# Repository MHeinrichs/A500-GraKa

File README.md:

[This project moved to gitlab on the day M$ bought github](https://gitlab.com/MHeinrichs/A500-GraKa)

The new repository is at: https://gitlab.com/MHeinrichs/A500-GraKa

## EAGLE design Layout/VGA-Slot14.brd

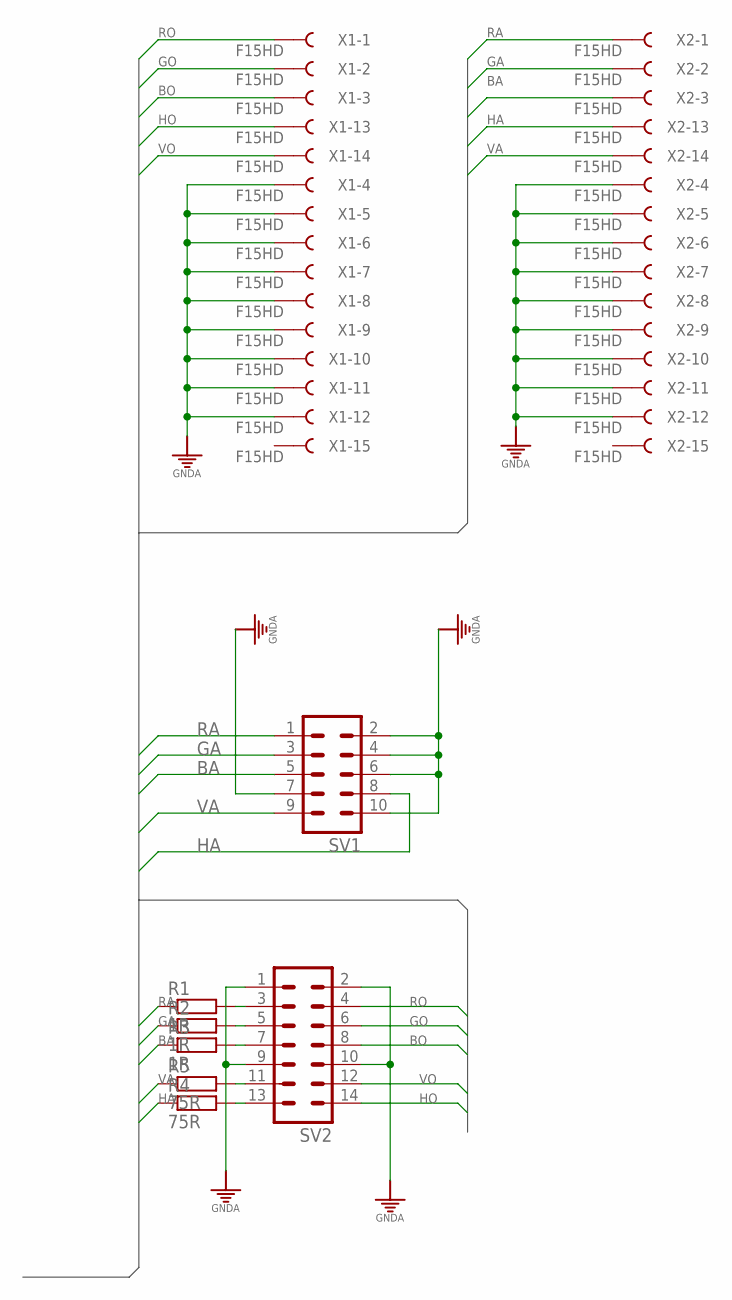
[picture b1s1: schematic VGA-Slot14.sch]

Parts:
R1, R2, R3: 1R; R0805
R4, R5: 75R; R0805
SV1: ML10
SV2: ML14
X1, X2: F15HD

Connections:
BA: R3.1, SV1.5, X2.3
BO: SV2.8, X1.3
GA: R2.1, SV1.3, X2.2
GNDA: SV1.2, SV1.4, SV1.6, SV1.7, SV1.10, SV2.1, SV2.2, SV2.9, SV2.10, X1.4, X1.5, X1.6, X1.7, X1.8, X1.9, X1.10, X1.11, X1.12, X2.4, X2.5, X2.6, X2.7, X2.8, X2.9, X2.10, X2.11, X2.12
GO: SV2.6, X1.2
HA: R4.1, SV1.8, X2.13
HO: SV2.14, X1.13
unnamed: R2.2, SV2.5
unnamed: R1.2, SV2.3
unnamed: R3.2, SV2.7
unnamed: R5.2, SV2.11
unnamed: R4.2, SV2.13
RA: R1.1, SV1.1, X2.1
RO: SV2.4, X1.1
VA: R5.1, SV1.9, X2.14
VO: SV2.12, X1.14

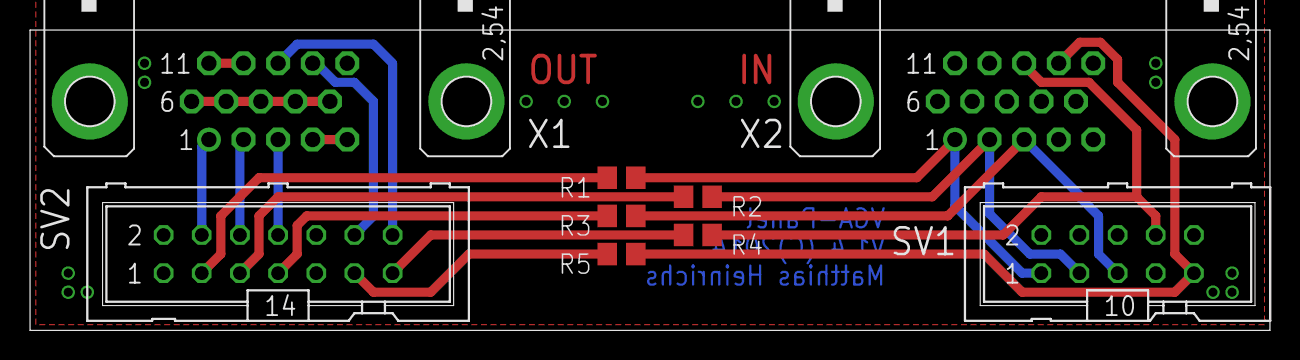
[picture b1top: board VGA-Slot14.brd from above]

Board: 2 copper layers, 82.5 x 20.0 mm, 9 parts (0 on the bottom side), 16 nets.

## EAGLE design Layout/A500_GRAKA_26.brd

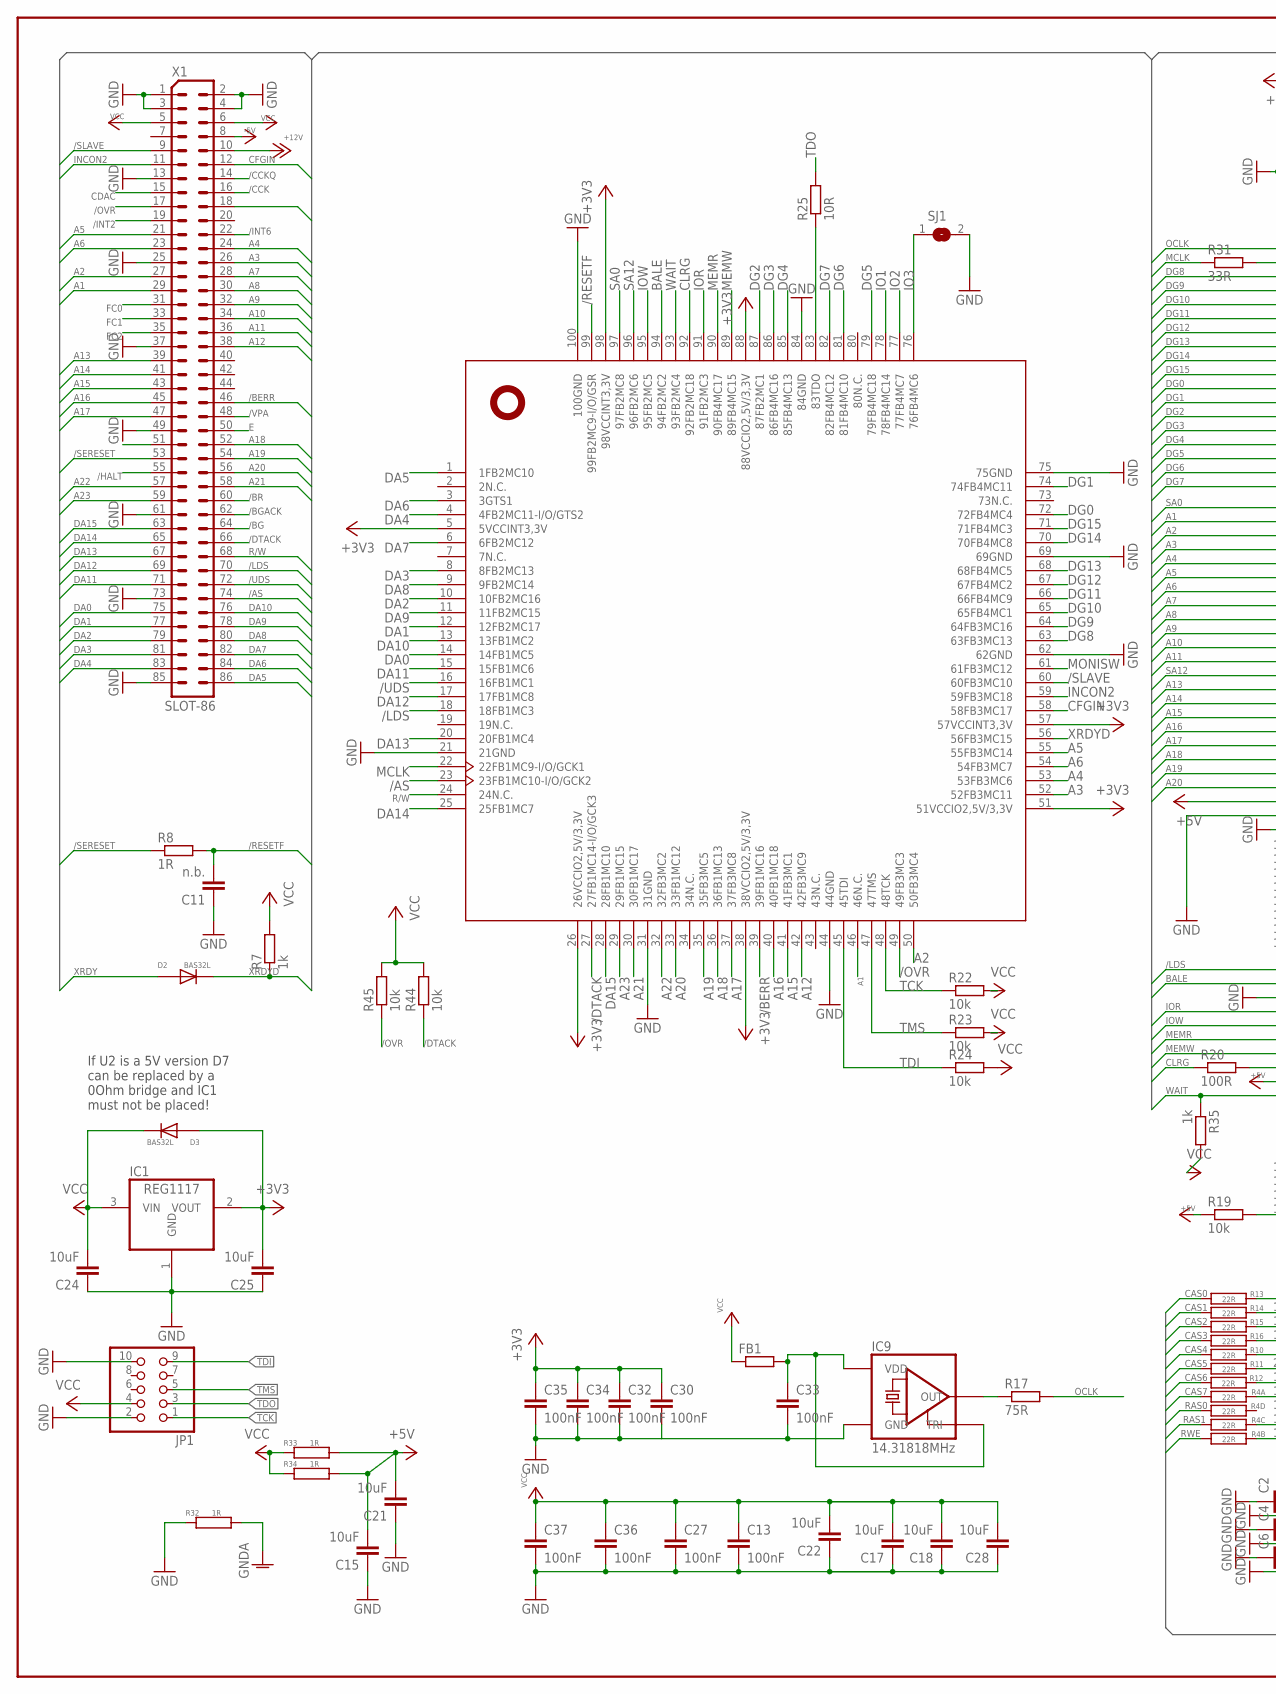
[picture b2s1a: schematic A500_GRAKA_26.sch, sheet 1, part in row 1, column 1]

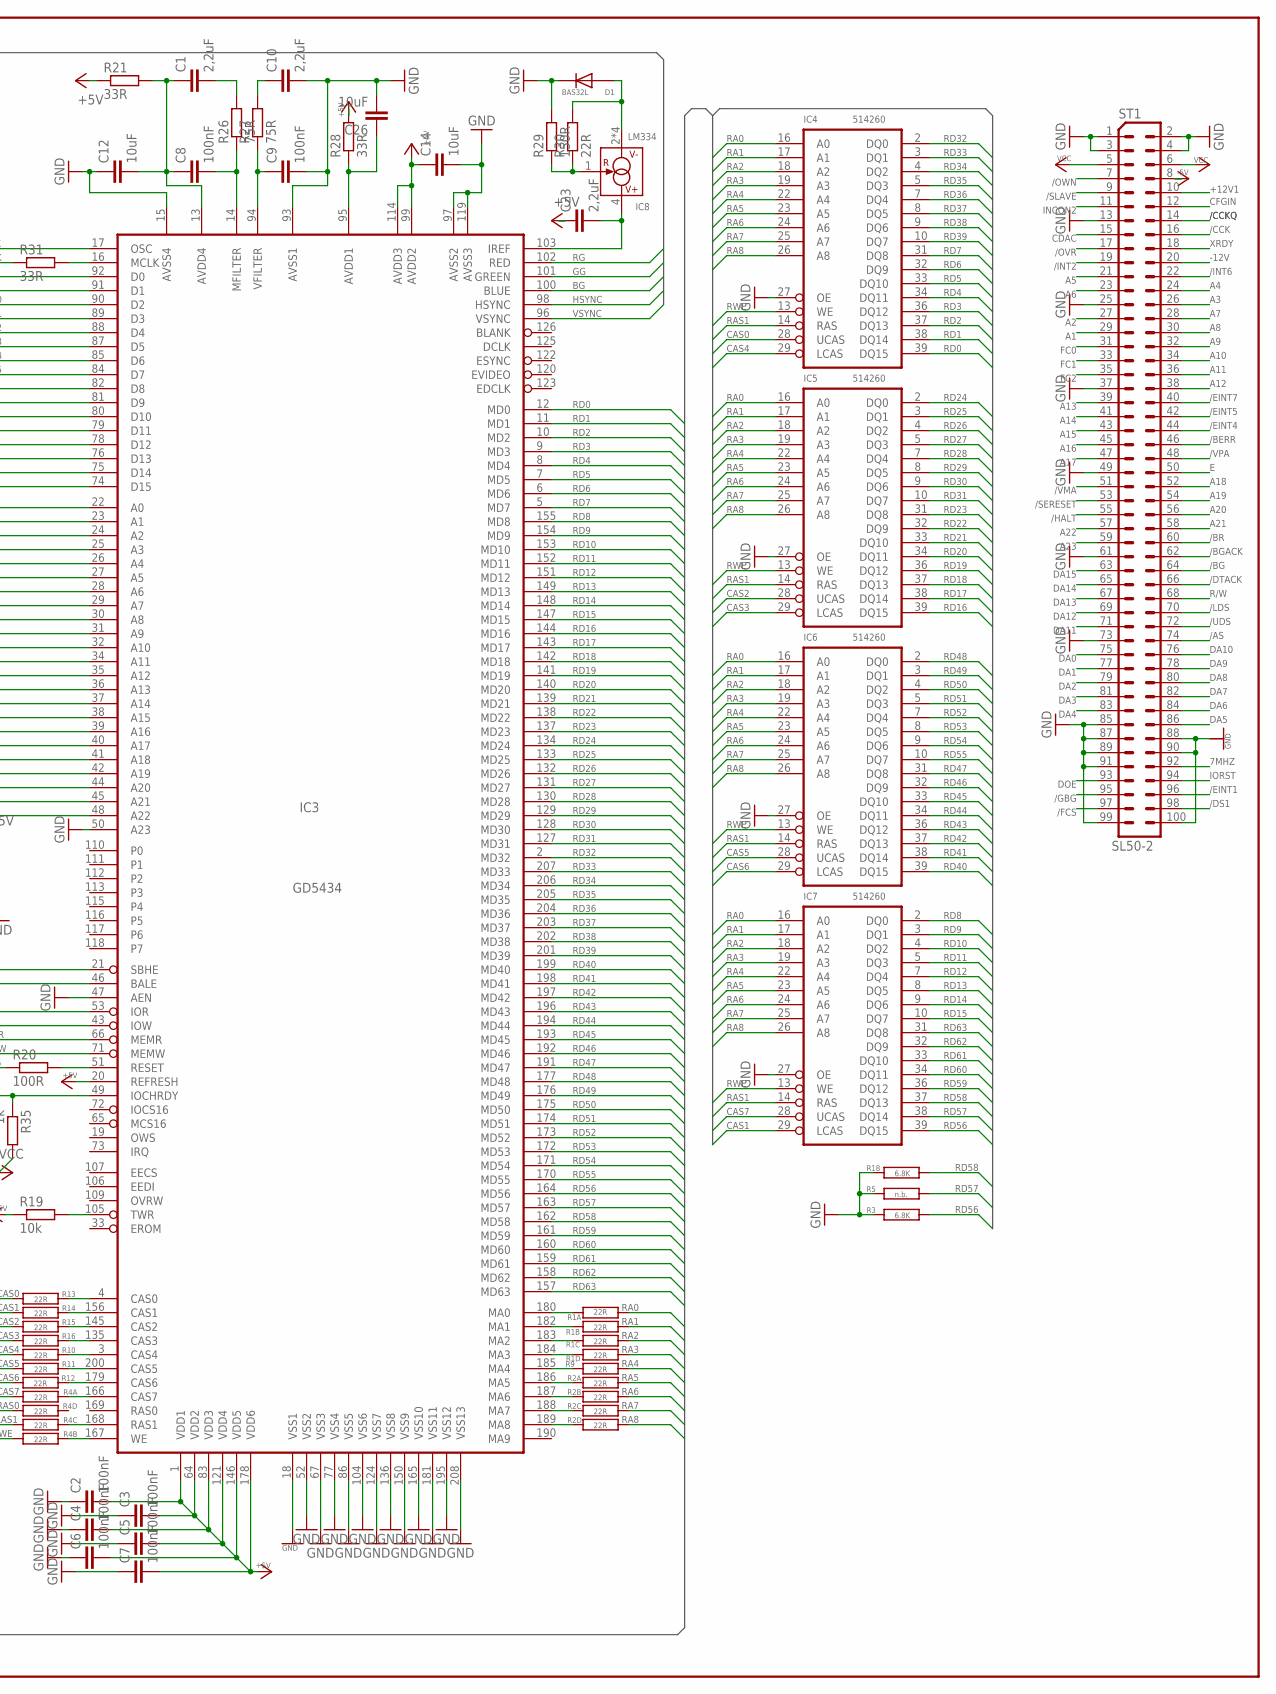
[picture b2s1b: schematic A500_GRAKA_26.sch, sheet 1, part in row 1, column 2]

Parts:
C1, C10, C23: 2,2uF; C0805K
C2, C3, C4, C5, C6, C7, C8, C9, C13, C27, C30, C32, C33, C34, C35, C36, C37: 100nF; C0805K
C11: n.b.; C0805K
C12, C14, C15, C17, C18, C21, C22, C24, C25, C26, C28: 10uF; C0805K
D1, D2, D3: BAS32L; SOD-80
FB1: R-EU_R0805; R0805
IC1: REG1117; SOT223
IC2: XC95144XLTQ100; TQ100
IC3: GD5434; PQFP-208@3
IC4, IC5, IC6, IC7: 514260; SOJ40/4
IC8: LM334; SO08
IC9: 14.31818MHz; 7X5
JP1: PINHD-2X5_2.54-SMD; 2X05SMD
R1, R2, R4: 22R; R-NETZ
R3, R18: 6.8K; 0805@2
R5: n.b.; 0805@2
R7, R35: 1k; R0805
R8: 1R; R0805
R9, R10, R11, R12, R13, R14, R15, R16: 22R; 0805@2
R17, R26, R27: 75R; R0805
R19, R22, R23, R24, R44, R45: 10k; R0805
R20: 100R; R0805
R21, R28, R31: 33R; R0805
R25: 10R; R0805
R29: 150R; R0805
R30: 22R; R0805
R32, R33, R34: 1R; 0204
SJ1: SJ
ST1: SL50-2; LKOT-501
X1: SLOT-86

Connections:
7MHZ: ST1.92
+3V3: C25.2, C30.1, C32.1, C34.1, C35.1, D3.1 (A), IC1.2 (VOUT), IC2.5 (5VCCINT3,3V), IC2.26 (26VCCIO2,5V/3,3V), IC2.38 (38VCCIO2,5V/3,3V), IC2.51 (51VCCIO2,5V/3,3V), IC2.57 (57VCCINT3,3V), IC2.88 (88VCCIO2,5V/3,3V), IC2.98 (98VCCINT3,3V)
+5V: C2.2, C3.2, C4.2, C5.2, C6.2, C7.2, C14.1, C15.2, C21.2, C23.1, IC3.1 (VDD1), IC3.20 (REFRESH), IC3.45 (A21), IC3.64 (VDD2), IC3.83 (VDD3), IC3.99 (AVDD2), IC3.114 (AVDD3), IC3.121 (VDD4), IC3.146 (VDD5), IC3.178 (VDD6), R19.1, R21.1, R28.2, R33.1, R34.1
+12V: X1.10
+12V1: ST1.10
-5V: ST1.8, X1.8
-12V: ST1.20
/AS: IC2.23 (23FB1MC10-I/O/GCK2), ST1.74, X1.74
/BERR: IC2.39 (39FB1MC16), ST1.46, X1.46
/BG: ST1.64, X1.64
/BGACK: ST1.62, X1.62
/BR: ST1.60, X1.60
/CCK: ST1.16, X1.16
/CCKQ: ST1.14, X1.14
/DS1: ST1.98
/DTACK: IC2.27 (27FB1MC14-I/O/GCK3), R44.1, ST1.66, X1.66
/EINT1: ST1.96
/EINT4: ST1.44
/EINT5: ST1.42
/EINT7: ST1.40
/FCS: ST1.97
/GBG: ST1.95
/HALT: ST1.55, X1.55
/INT2: ST1.19, X1.19
/INT6: ST1.22, X1.22
/LDS: IC2.18 (18FB1MC3), IC3.21 (SBHE), ST1.70, X1.70
/OVR: IC2.49 (49FB3MC3), R45.1, ST1.17, X1.17
/OWN: ST1.7
/RESETF: C11.2, IC2.99 (99FB2MC9-I/O/GSR), R8.2
/SERESET: R8.1, ST1.53, X1.53
/SLAVE: IC2.60 (60FB3MC10), ST1.9, X1.9
/UDS: IC2.16 (16FB1MC1), ST1.72, X1.72
/VMA: ST1.51, X1.51
/VPA: ST1.48, X1.48
A1: IC2.46 (46N.C.), IC3.23 (A1), ST1.29, X1.29
A2: IC2.50 (50FB3MC4), IC3.24 (A2), ST1.27, X1.27
A3: IC2.52 (52FB3MC11), IC3.25 (A3), ST1.26, X1.26
A4: IC2.53 (53FB3MC6), IC3.26 (A4), ST1.24, X1.24
A5: IC2.55 (55FB3MC14), IC3.27 (A5), ST1.21, X1.21
A6: IC2.54 (54FB3MC7), IC3.28 (A6), ST1.23, X1.23
A7: IC3.29 (A7), ST1.28, X1.28
A8: IC3.30 (A8), ST1.30, X1.30
A9: IC3.31 (A9), ST1.32, X1.32
A10: IC3.32 (A10), ST1.34, X1.34
A11: IC3.34 (A11), ST1.36, X1.36
A12: IC2.42 (42FB3MC9), ST1.38, X1.38
A13: IC3.36 (A13), ST1.39, X1.39
A14: IC3.37 (A14), ST1.41, X1.41
A15: IC2.41 (41FB3MC1), IC3.38 (A15), ST1.43, X1.43
A16: IC2.40 (40FB1MC18), IC3.39 (A16), ST1.45, X1.45
A17: IC2.37 (37FB3MC8), IC3.40 (A17), ST1.47, X1.47
A18: IC2.36 (36FB1MC13), IC3.41 (A18), ST1.52, X1.52
A19: IC2.35 (35FB3MC5), IC3.42 (A19), ST1.54, X1.54
A20: IC2.33 (33FB1MC12), IC3.44 (A20), ST1.56, X1.56
A21: IC2.30 (30FB1MC17), ST1.58, X1.58
A22: IC2.32 (32FB3MC2), ST1.57, X1.57
A23: IC2.29 (29FB1MC15), ST1.59, X1.59
AVDD1: C26.1, IC3.95 (AVDD1), R28.1
AVDD4: C1.1, C8.1, C12.2, IC3.13 (AVDD4), R21.2
BALE: IC2.94 (94FB2MC2), IC3.46 (BALE)
BG: IC3.100 (BLUE); also elsewhere on the board
CAS0: IC4.28 (UCAS), R13.1
CAS1: IC7.29 (LCAS), R14.1
CAS2: IC5.28 (UCAS), R15.1
CAS3: IC5.29 (LCAS), R16.1
CAS4: IC4.29 (LCAS), R10.1
CAS5: IC6.28 (UCAS), R11.1
CAS6: IC6.29 (LCAS), R12.2
CAS7: IC7.28 (UCAS), R4.P$1
CDAC: ST1.15, X1.15
CFGIN: IC2.58 (58FB3MC17), ST1.12, X1.12
CLRG: IC2.92 (92FB2MC18), R20.1
DA0: IC2.14 (14FB1MC5), ST1.75, X1.75
DA1: IC2.12 (12FB2MC17), ST1.77, X1.77
DA2: IC2.10 (10FB2MC16), ST1.79, X1.79
DA3: IC2.8 (8FB2MC13), ST1.81, X1.81
DA4: IC2.4 (4FB2MC11-I/O/GTS2), ST1.83, X1.83
DA5: IC2.1 (1FB2MC10), ST1.86, X1.86
DA6: IC2.3 (3GTS1), ST1.84, X1.84
DA7: IC2.6 (6FB2MC12), ST1.82, X1.82
DA8: IC2.9 (9FB2MC14), ST1.80, X1.80
DA9: IC2.11 (11FB2MC15), ST1.78, X1.78
DA10: IC2.13 (13FB1MC2), ST1.76, X1.76
DA11: IC2.15 (15FB1MC6), ST1.71, X1.71
DA12: IC2.17 (17FB1MC8), ST1.69, X1.69
DA13: IC2.20 (20FB1MC4), ST1.67, X1.67
DA14: IC2.25 (25FB1MC7), ST1.65, X1.65
DA15: IC2.28 (28FB1MC10), ST1.63, X1.63
DG0: IC2.72 (72FB4MC4), IC3.82 (D8)
DG1: IC2.74 (74FB4MC11), IC3.81 (D9)
DG2: IC2.87 (87FB2MC1), IC3.80 (D10)
DG3: IC2.86 (86FB4MC16), IC3.79 (D11)
DG4: IC2.85 (85FB4MC13), IC3.78 (D12)
DG5: IC2.79 (79FB4MC18), IC3.76 (D13)
DG6: IC2.81 (81FB4MC10), IC3.75 (D14)
DG7: IC2.82 (82FB4MC12), IC3.74 (D15)
DG8: IC2.63 (63FB3MC13), IC3.92 (D0)
DG9: IC2.64 (64FB3MC16), IC3.91 (D1)
DG10: IC2.65 (65FB4MC1), IC3.90 (D2)
DG11: IC2.66 (66FB4MC9), IC3.89 (D3)
DG12: IC2.67 (67FB4MC2), IC3.88 (D4)
DG13: IC2.68 (68FB4MC5), IC3.87 (D5)
DG14: IC2.70 (70FB4MC8), IC3.85 (D6)
DG15: IC2.71 (71FB4MC3), IC3.84 (D7)
DOE: ST1.93
E: ST1.50, X1.50
FC0: ST1.31, X1.31
FC1: ST1.33, X1.33
FC2: ST1.35, X1.35
GG: IC3.101 (GREEN); also elsewhere on the board
GND: C2.1, C3.1, C4.1, C5.1, C6.1, C7.1, C9.2, C10.2, C11.1, C12.1, C13.2, C14.2, C15.1, C17.1, C18.1, C21.1, C22.1, C24.1, C25.1, C26.2, C27.2, C28.1, C30.2, C32.2, C33.2, C34.2, C35.2, C36.2, C37.2, D1.2 (K), IC1.1 (GND), IC2.21 (21GND), IC2.31 (31GND), IC2.44 (44GND), IC2.62 (62GND), IC2.69 (69GND), IC2.75 (75GND), IC2.84 (84GND), IC2.100 (100GND), IC3.15 (AVSS4), IC3.18 (VSS1), IC3.47 (AEN), IC3.48 (A22), IC3.50 (A23), IC3.52 (VSS2), IC3.67 (VSS3), IC3.77 (VSS4), IC3.86 (VSS5), IC3.93 (AVSS1), IC3.97 (AVSS2), IC3.104 (VSS6), IC3.119 (AVSS3), IC3.124 (VSS7), IC3.136 (VSS8), IC3.150 (VSS9), IC3.165 (VSS10), IC3.181 (VSS11), IC3.195 (VSS12), IC3.208 (VSS13), IC4.21 (GND), IC4.27 (OE), IC4.35 (GND), IC4.40 (GND), IC5.21 (GND), IC5.27 (OE), IC5.35 (GND), IC5.40 (GND), IC6.21 (GND), IC6.27 (OE), IC6.35 (GND), IC6.40 (GND), IC7.21 (GND), IC7.27 (OE), IC7.35 (GND), IC7.40 (GND), IC9.P$2 (GND), JP1.2, JP1.10, R3.2, R5.2, R18.2, R29.2, R32.2, SJ1.2, ST1.1, ST1.2, ST1.3, ST1.4, ST1.13, ST1.25, ST1.37, ST1.49, ST1.61, ST1.73, ST1.85, ST1.87, ST1.88, ST1.89, ST1.90, ST1.91, ST1.99, ST1.100, X1.1, X1.2, X1.3, X1.4, X1.13, X1.25, X1.37, X1.49, X1.61, X1.73, X1.85; also elsewhere on the board
GNDA: R32.1; also elsewhere on the board
HSYNC: IC3.98 (HSYNC); also elsewhere on the board
INCON2: IC2.59 (59FB3MC18), ST1.11, X1.11
IO1: IC2.78 (78FB4MC14)
IO2: IC2.77 (77FB4MC7)
IO3: IC2.76 (76FB4MC6), SJ1.1
IOR: IC2.91 (91FB2MC3), IC3.53 (IOR)
IORST: ST1.94
IOW: IC2.95 (95FB2MC5), IC3.43 (IOW)
MCLK: IC2.22 (22FB1MC9-I/O/GCK1), R31.1
MEMR: IC2.90 (90FB4MC17), IC3.66 (MEMR)
MEMW: IC2.89 (89FB4MC15), IC3.71 (MEMW)
MONISW: IC2.61 (61FB3MC12); also elsewhere on the board
unnamed: IC3.185 (MA4), R9.2
unnamed: IC3.180 (MA0), R1.P$8
unnamed: IC3.182 (MA1), R1.P$7
unnamed: IC3.186 (MA5), R2.P$8
unnamed: IC3.187 (MA6), R2.P$7
unnamed: IC3.188 (MA7), R2.P$6
unnamed: IC3.189 (MA8), R2.P$5
unnamed: IC3.183 (MA2), R1.P$6
unnamed: C33.1, FB1.2, IC9.P$1 (TRI), IC9.P$4 (VDD)
unnamed: IC3.184 (MA3), R1.P$5
unnamed: IC3.3 (CAS4), R10.2
unnamed: IC3.200 (CAS5), R11.2
unnamed: IC3.179 (CAS6), R12.1
unnamed: IC3.4 (CAS0), R13.2
unnamed: IC3.156 (CAS1), R14.2
unnamed: IC3.145 (CAS2), R15.2
unnamed: IC3.135 (CAS3), R16.2
unnamed: IC3.16 (MCLK), R31.2
unnamed: IC9.P$3 (OUT), R17.1
unnamed: C1.2, R26.2
unnamed: C8.2, IC3.14 (MFILTER), R26.1
unnamed: C9.1, IC3.94 (VFILTER), R27.1
unnamed: IC3.51 (RESET), R20.2
unnamed: C10.1, R27.2
unnamed: C23.2, IC3.103 (IREF), IC8.4 (V+)
unnamed: IC8.1 (R), R29.1, R30.1
unnamed: D1.1 (A), IC8.2 (V-), IC8.3 (V-), IC8.6 (V-), IC8.7 (V-), R30.2
unnamed: IC3.105 (TWR), R19.2
unnamed: IC3.166 (CAS7), R4.P$8
unnamed: IC3.168 (RAS1), R4.P$6
unnamed: IC3.167 (WE), R4.P$7
OCLK: IC3.17 (OSC), R17.2
R/W: IC2.24 (24N.C.), ST1.68, X1.68
RA0: IC4.16 (A0), IC5.16 (A0), IC6.16 (A0), IC7.16 (A0), R1.P$1
RA1: IC4.17 (A1), IC5.17 (A1), IC6.17 (A1), IC7.17 (A1), R1.P$2
RA2: IC4.18 (A2), IC5.18 (A2), IC6.18 (A2), IC7.18 (A2), R1.P$3
RA3: IC4.19 (A3), IC5.19 (A3), IC6.19 (A3), IC7.19 (A3), R1.P$4
RA4: IC4.22 (A4), IC5.22 (A4), IC6.22 (A4), IC7.22 (A4), R9.1
RA5: IC4.23 (A5), IC5.23 (A5), IC6.23 (A5), IC7.23 (A5), R2.P$1
RA6: IC4.24 (A6), IC5.24 (A6), IC6.24 (A6), IC7.24 (A6), R2.P$2
RA7: IC4.25 (A7), IC5.25 (A7), IC6.25 (A7), IC7.25 (A7), R2.P$3
RA8: IC4.26 (A8), IC5.26 (A8), IC6.26 (A8), IC7.26 (A8), R2.P$4
RAS0: R4.P$4
RAS1: IC4.14 (RAS), IC5.14 (RAS), IC6.14 (RAS), IC7.14 (RAS), R4.P$3
RD0: IC3.12 (MD0), IC4.39 (DQ15)
RD1: IC3.11 (MD1), IC4.38 (DQ14)
RD2: IC3.10 (MD2), IC4.37 (DQ13)
RD3: IC3.9 (MD3), IC4.36 (DQ12)
RD4: IC3.8 (MD4), IC4.34 (DQ11)
RD5: IC3.7 (MD5), IC4.33 (DQ10)
RD6: IC3.6 (MD6), IC4.32 (DQ9)
RD7: IC3.5 (MD7), IC4.31 (DQ8)
RD8: IC3.155 (MD8), IC7.2 (DQ0)
RD9: IC3.154 (MD9), IC7.3 (DQ1)
RD10: IC3.153 (MD10), IC7.4 (DQ2)
RD11: IC3.152 (MD11), IC7.5 (DQ3)
RD12: IC3.151 (MD12), IC7.7 (DQ4)
RD13: IC3.149 (MD13), IC7.8 (DQ5)
RD14: IC3.148 (MD14), IC7.9 (DQ6)
RD15: IC3.147 (MD15), IC7.10 (DQ7)
RD16: IC3.144 (MD16), IC5.39 (DQ15)
RD17: IC3.143 (MD17), IC5.38 (DQ14)
RD18: IC3.142 (MD18), IC5.37 (DQ13)
RD19: IC3.141 (MD19), IC5.36 (DQ12)
RD20: IC3.140 (MD20), IC5.34 (DQ11)
RD21: IC3.139 (MD21), IC5.33 (DQ10)
RD22: IC3.138 (MD22), IC5.32 (DQ9)
RD23: IC3.137 (MD23), IC5.31 (DQ8)
RD24: IC3.134 (MD24), IC5.2 (DQ0)
RD25: IC3.133 (MD25), IC5.3 (DQ1)
RD26: IC3.132 (MD26), IC5.4 (DQ2)
RD27: IC3.131 (MD27), IC5.5 (DQ3)
RD28: IC3.130 (MD28), IC5.7 (DQ4)
RD29: IC3.129 (MD29), IC5.8 (DQ5)
RD30: IC3.128 (MD30), IC5.9 (DQ6)
RD31: IC3.127 (MD31), IC5.10 (DQ7)
RD32: IC3.2 (MD32), IC4.2 (DQ0)
RD33: IC3.207 (MD33), IC4.3 (DQ1)
RD34: IC3.206 (MD34), IC4.4 (DQ2)
RD35: IC3.205 (MD35), IC4.5 (DQ3)
RD36: IC3.204 (MD36), IC4.7 (DQ4)
RD37: IC3.203 (MD37), IC4.8 (DQ5)
RD38: IC3.202 (MD38), IC4.9 (DQ6)
RD39: IC3.201 (MD39), IC4.10 (DQ7)
RD40: IC3.199 (MD40), IC6.39 (DQ15)
RD41: IC3.198 (MD41), IC6.38 (DQ14)
RD42: IC3.197 (MD42), IC6.37 (DQ13)
RD43: IC3.196 (MD43), IC6.36 (DQ12)
RD44: IC3.194 (MD44), IC6.34 (DQ11)
RD45: IC3.193 (MD45), IC6.33 (DQ10)
RD46: IC3.192 (MD46), IC6.32 (DQ9)
RD47: IC3.191 (MD47), IC6.31 (DQ8)
RD48: IC3.177 (MD48), IC6.2 (DQ0)
RD49: IC3.176 (MD49), IC6.3 (DQ1)
RD50: IC3.175 (MD50), IC6.4 (DQ2)
RD51: IC3.174 (MD51), IC6.5 (DQ3)
RD52: IC3.173 (MD52), IC6.7 (DQ4)
RD53: IC3.172 (MD53), IC6.8 (DQ5)
RD54: IC3.171 (MD54), IC6.9 (DQ6)
RD55: IC3.170 (MD55), IC6.10 (DQ7)
RD56: IC3.164 (MD56), IC7.39 (DQ15), R3.1
RD57: IC3.163 (MD57), IC7.38 (DQ14), R5.1
RD58: IC3.162 (MD58), IC7.37 (DQ13), R18.1
RD59: IC3.161 (MD59), IC7.36 (DQ12)
RD60: IC3.160 (MD60), IC7.34 (DQ11)
RD61: IC3.159 (MD61), IC7.33 (DQ10)
RD62: IC3.158 (MD62), IC7.32 (DQ9)
RD63: IC3.157 (MD63), IC7.31 (DQ8)
RG: IC3.102 (RED); also elsewhere on the board
RWE: IC4.13 (WE), IC5.13 (WE), IC6.13 (WE), IC7.13 (WE), R4.P$2
SA0: IC2.97 (97FB2MC8), IC3.22 (A0)
SA12: IC2.96 (96FB2MC6), IC3.35 (A12)
TCK: IC2.48 (48TCK), JP1.1, R22.1
TDI: IC2.45 (45TDI), JP1.9, R24.1
TDO: JP1.3, R25.2
TDO1: IC2.83 (83TDO), R25.1
TMS: IC2.47 (47TMS), JP1.5, R23.1
VCC: C13.1, C17.2, C18.2, C22.2, C24.2, C27.1, C28.2, C36.1, C37.1, D3.2 (K), FB1.1, IC1.3 (VIN), IC4.1 (VCC), IC4.6 (VCC), IC4.20 (VCC), IC5.1 (VCC), IC5.6 (VCC), IC5.20 (VCC), IC6.1 (VCC), IC6.6 (VCC), IC6.20 (VCC), IC7.1 (VCC), IC7.6 (VCC), IC7.20 (VCC), JP1.4, R7.2, R22.2, R23.2, R24.2, R33.2, R34.2, R35.2, R44.2, R45.2, ST1.5, ST1.6, X1.5, X1.6; also elsewhere on the board
VSYNC: IC3.96 (VSYNC); also elsewhere on the board
WAIT: IC2.93 (93FB2MC4), IC3.49 (IOCHRDY), R35.1
XRDY: D2.1 (A), ST1.18, X1.18
XRDYD: D2.2 (K), IC2.56 (56FB3MC15), R7.1

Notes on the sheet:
If U2 is a 5V version D7 can be replaced by a 0Ohm bridge and IC1 must not be placed!
-12V
/CCKQ
/CCK
/INT6
/VPA
/EINT7
/EINT5
/EINT4
/BG
/BGACK
/DTACK
/BR

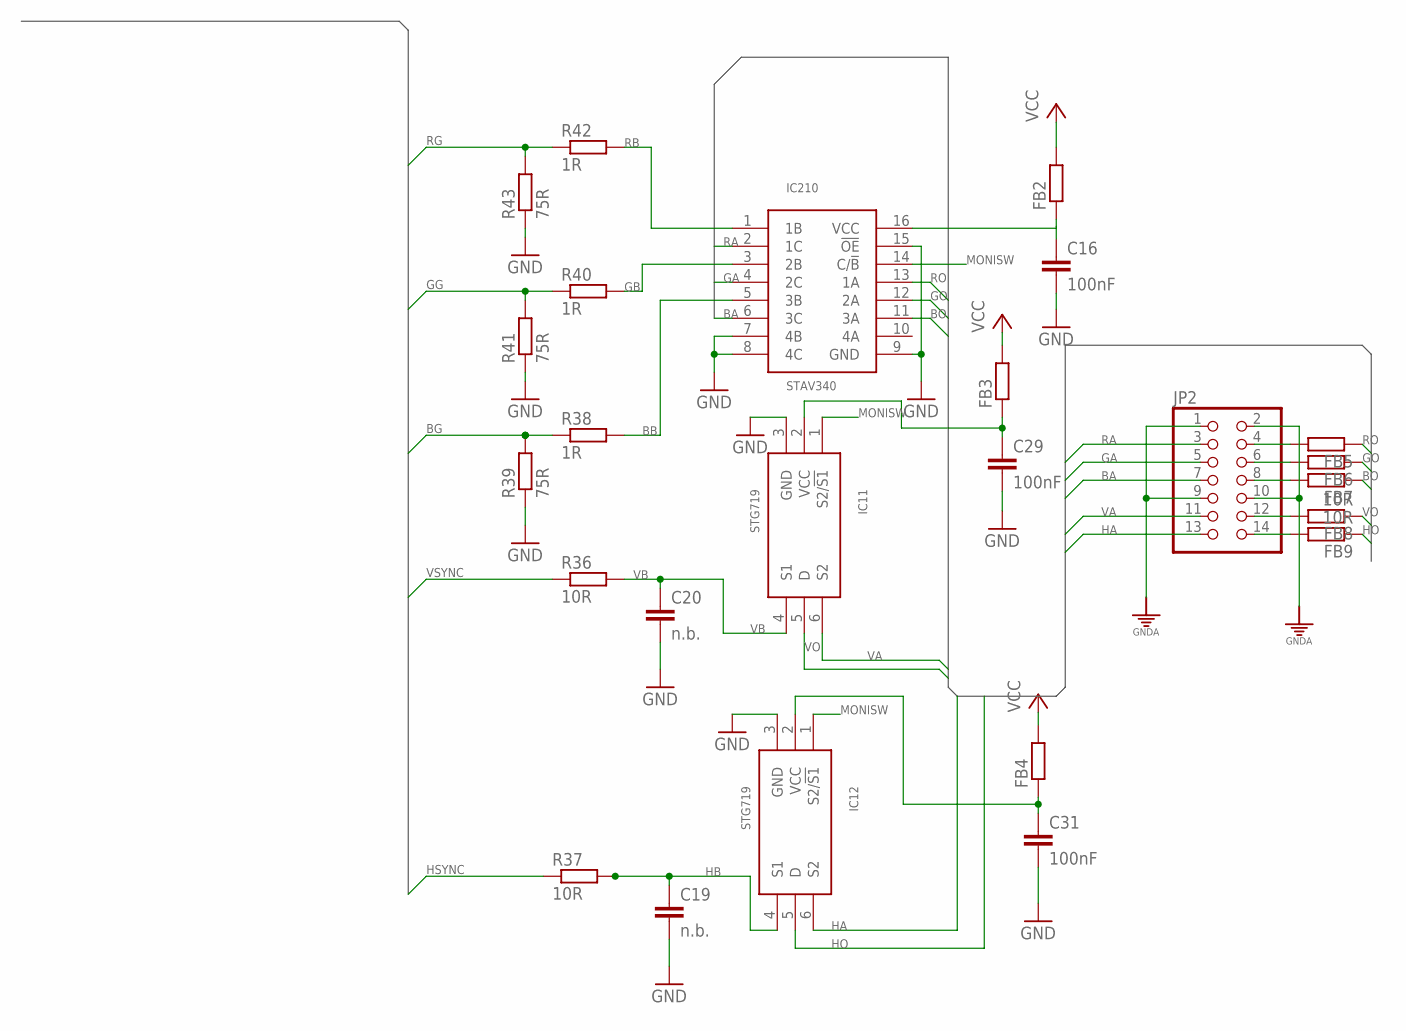
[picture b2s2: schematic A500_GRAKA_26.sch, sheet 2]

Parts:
C16, C29, C31: 100nF; C0805K
C19, C20: n.b.; C0805K
FB2, FB3, FB4, FB5, FB6, FB7: R-EU_R0805; R0805
FB8, FB9: 10R; R0805
IC11, IC12: STG719; SOT23-6L
IC210: STAV340; TSSOP16
JP2: PINHD-2X7_2.54-SMD; 2X07SMD
R36, R37: 10R; R0805
R38, R40, R42: 1R; R0805
R39, R41, R43: 75R; R0805

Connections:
BA: IC210.6 (3C), JP2.7
BB: IC210.5 (3B), R38.2
BG: R38.1, R39.2; also elsewhere on the board
BO: FB7.1, IC210.11 (3A)
GA: IC210.4 (2C), JP2.5
GB: IC210.3 (2B), R40.2
GG: R40.1, R41.2; also elsewhere on the board
GND: C16.2, C19.2, C20.2, C29.2, C31.2, IC11.3 (GND), IC12.3 (GND), IC210.7 (4B), IC210.8 (4C), IC210.9 (GND), IC210.15 (!OE), R39.1, R41.1, R43.1; also elsewhere on the board
GNDA: JP2.1, JP2.2, JP2.9, JP2.10; also elsewhere on the board
GO: FB6.1, IC210.12 (2A)
HA: IC12.6 (S2), JP2.13
HB: C19.1, IC12.4 (S1), R37.2
HO: FB9.1, IC12.5 (D)
HSYNC: R37.1; also elsewhere on the board
MONISW: IC11.1 (S2/!S1), IC12.1 (S2/!S1), IC210.14 (C/!B); also elsewhere on the board
unnamed: C16.1, FB2.1, IC210.16 (VCC)
unnamed: FB7.2, JP2.8
unnamed: C29.1, FB3.1, IC11.2 (VCC)
unnamed: C31.1, FB4.1, IC12.2 (VCC)
unnamed: FB6.2, JP2.6
unnamed: FB5.2, JP2.4
unnamed: FB8.2, JP2.12
unnamed: FB9.2, JP2.14
RA: IC210.2 (1C), JP2.3
RB: IC210.1 (1B), R42.2
RG: R42.1, R43.2; also elsewhere on the board
RO: FB5.1, IC210.13 (1A)
VA: IC11.6 (S2), JP2.11
VB: C20.1, IC11.4 (S1), R36.2
VCC: FB2.2, FB3.2, FB4.2; also elsewhere on the board
VO: FB8.1, IC11.5 (D)
VSYNC: R36.1; also elsewhere on the board

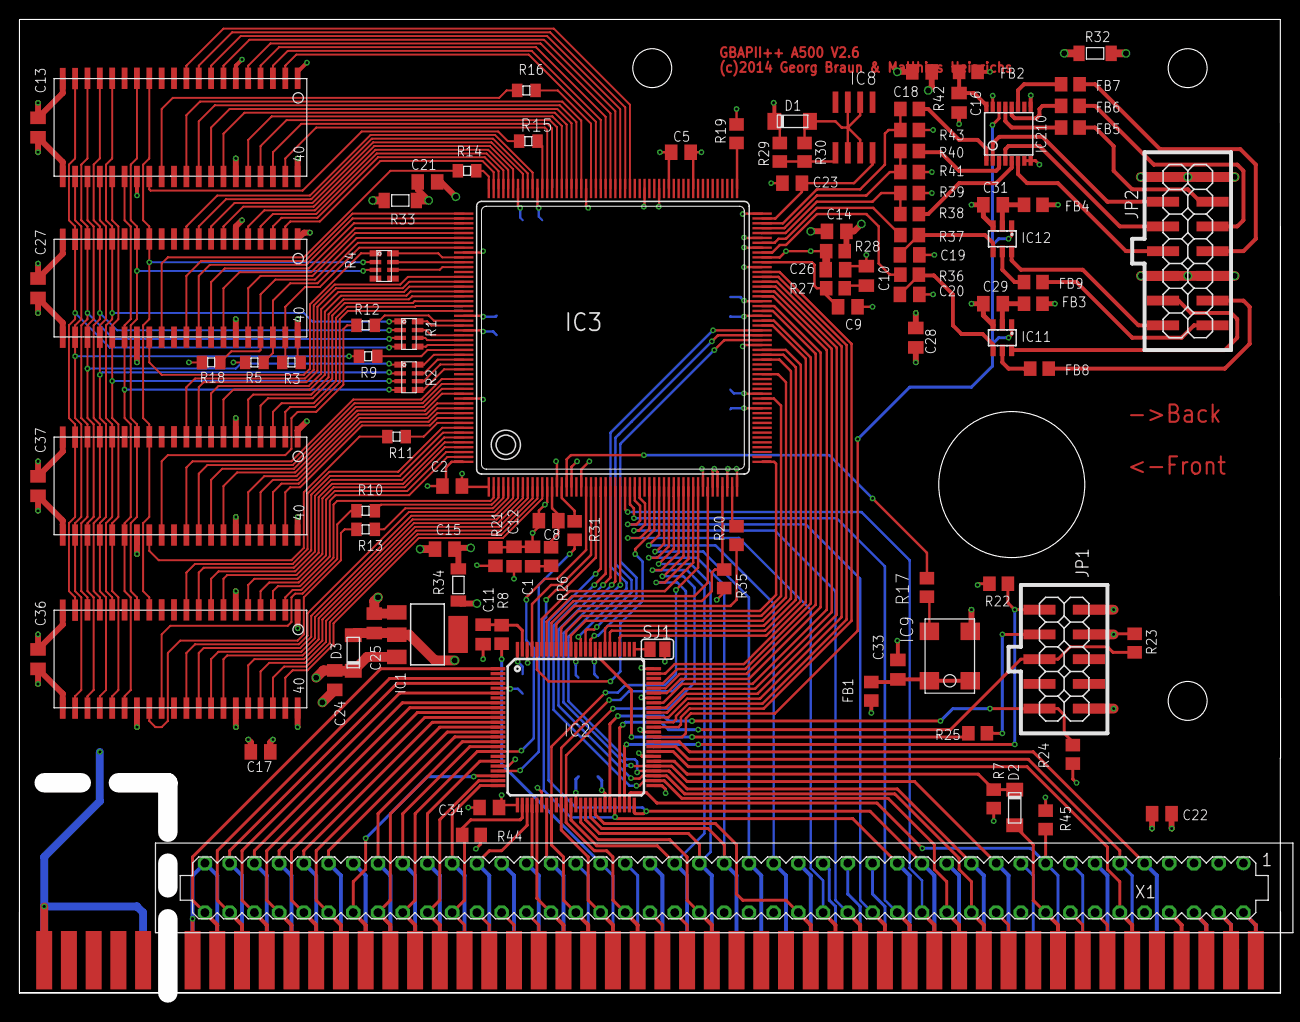
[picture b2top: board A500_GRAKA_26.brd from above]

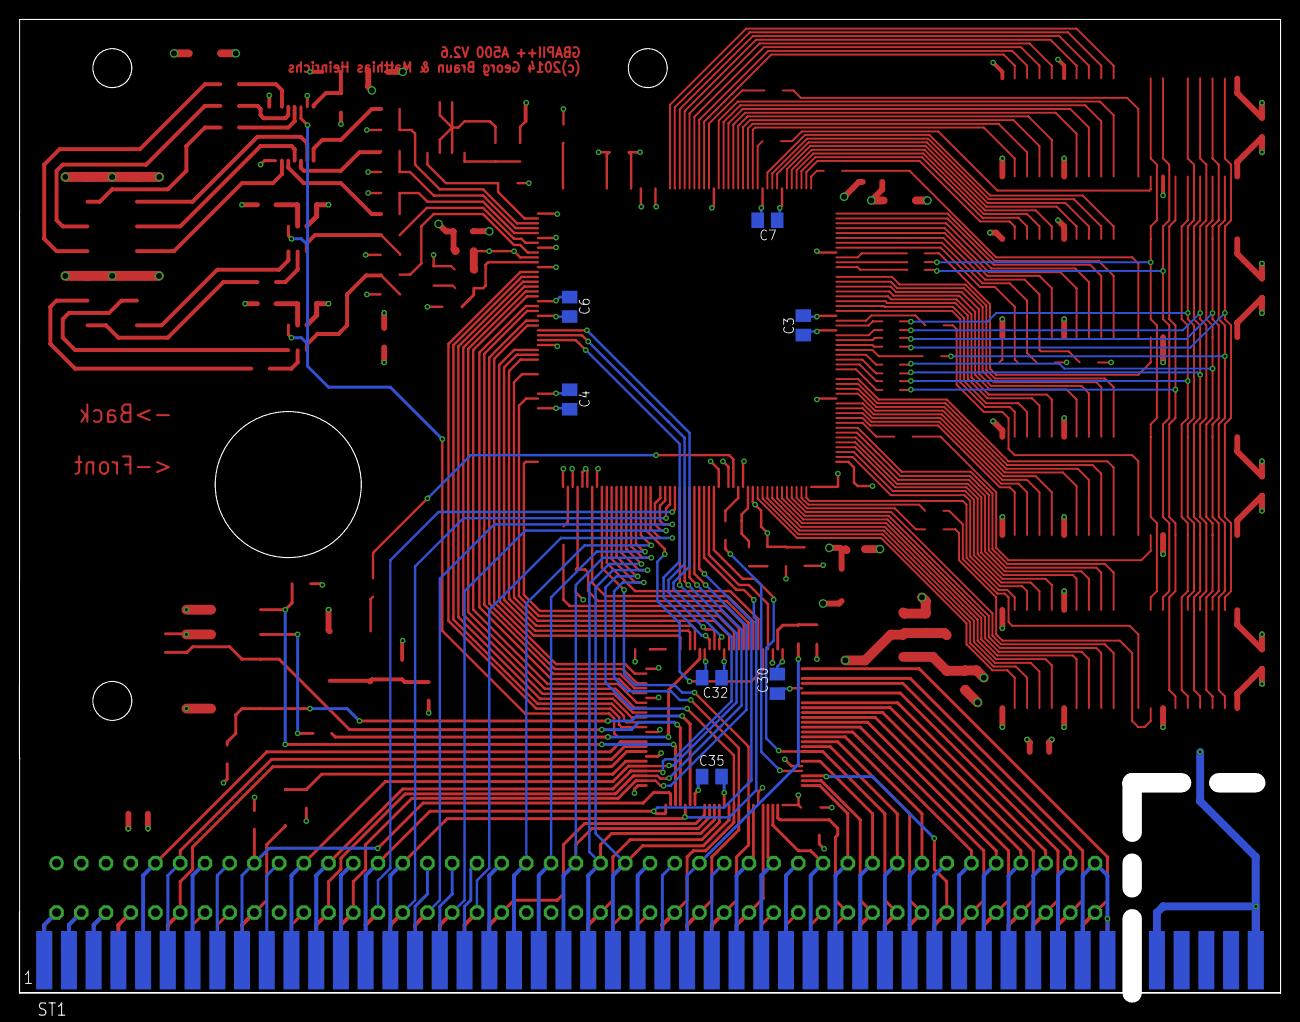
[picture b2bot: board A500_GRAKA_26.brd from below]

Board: 4 copper layers, 129.5 x 100.0 mm, 110 parts (8 on the bottom side), 252 nets.

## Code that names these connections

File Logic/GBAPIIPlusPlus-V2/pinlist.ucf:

#PIN MAP for the gbap2++
NET reset LOC = "P99";
NET "SA0" LOC = "P97";
NET "SA12" LOC = "P96";
NET "IOW" LOC = "P95";
NET "BALE" LOC = "P94";
NET "WAIT" LOC = "P93";
NET "CLRG" LOC = "P92";
NET "IOR" LOC = "P91";
NET "MEMR" LOC = "P90";
NET "MEMW" LOC = "P89";
NET "DG[2]" LOC = "P87";
NET "DG[3]" LOC = "P86";
NET "DG[4]" LOC = "P85";
NET "DG[7]" LOC = "P82";
NET "DG[6]" LOC = "P81";
NET "DG[5]" LOC = "P79";
NET "IO[1]" LOC = "P78";
NET "IO[2]" LOC = "P77";
NET "IO[3]" LOC = "P76";
NET "DG[1]" LOC = "P74";
NET "DG[0]" LOC = "P72";
NET "DG[15]" LOC = "P71";
NET "DG[14]" LOC = "P70";
NET "DG[13]" LOC = "P68";
NET "DG[12]" LOC = "P67";
NET "DG[11]" LOC = "P66";
NET "DG[10]" LOC = "P65";
NET "DG[9]" LOC = "P64";
NET "DG[8]" LOC = "P63";
NET "MONISW" LOC = "P61";
NET "SLAVE" LOC = "P60";
NET "CFGOUT" LOC = "P59";
NET "CFGIN" LOC = "P58";
NET "XRDYD" LOC = "P56";
NET "A[5]" LOC = "P55";
NET "A[6]" LOC = "P54";
NET "A[4]" LOC = "P53";
NET "A[3]" LOC = "P52";
NET "A[2]" LOC = "P50";
NET "OVR" LOC = "P49"; 
NET "A[1]" LOC = "P46"; 
NET "A[12]" LOC = "P42";
NET "A[15]" LOC = "P41";
NET "A[16]" LOC = "P40";
NET "BERR" LOC = "P39";
NET "A[17]" LOC = "P37";
NET "A[18]" LOC = "P36";
NET "A[19]" LOC = "P35";
NET "A[20]" LOC = "P33";
NET "A[22]" LOC = "P32";
NET "A[21]" LOC = "P30";
NET "A[23]" LOC = "P29"; 
NET "DA[15]" LOC = "P28";
NET "DTACK" LOC = "P27";
NET "DA[14]" LOC = "P25";
NET "RW" LOC = "P24";
NET "AS" LOC = "P23";
NET "mclk" LOC = "P22";
NET "DA[13]" LOC = "P20";
NET "LDS" LOC = "P18";
NET "DA[12]" LOC = "P17";
NET "UDS" LOC = "P16";
NET "DA[11]" LOC = "P15";
NET "DA[0]" LOC = "P14";
NET "DA[10]" LOC = "P13";
NET "DA[1]" LOC = "P12";
NET "DA[9]" LOC = "P11";
NET "DA[2]" LOC = "P10";
NET "DA[8]" LOC = "P9";
NET "DA[3]" LOC = "P8";
NET "DA[7]" LOC = "P6";
NET "DA[4]" LOC = "P4";
NET "DA[6]" LOC = "P3";
NET "DA[5]" LOC = "P1";

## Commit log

2014-08-15 :boom::camel: Added .gitattributes
2014-08-15 Initial Version
2014-08-17 Still buggy
2014-08-17 Error found: 16-R/W (not fixed)!
2014-08-18 Stable RAM design...
2014-08-21 Working!
2014-08-26 Workng on GBA-Rev4-060
2015-02-03 DTACK enabled, BCBs added, Driver Added
2015-02-19 Some Updates and timing optimized
2015-06-26 Misc Updates
2016-05-29 Some tries to make the Card look like a PiccoloSD64
2019-08-28 Moved to gitlab

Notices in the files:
Layout/A500_GRAKA_26.brd:
(c)2014 Georg Braun & Matthias Heinrichs
Layout/VGA-Slot14.brd:
V1.4 (C)2014
